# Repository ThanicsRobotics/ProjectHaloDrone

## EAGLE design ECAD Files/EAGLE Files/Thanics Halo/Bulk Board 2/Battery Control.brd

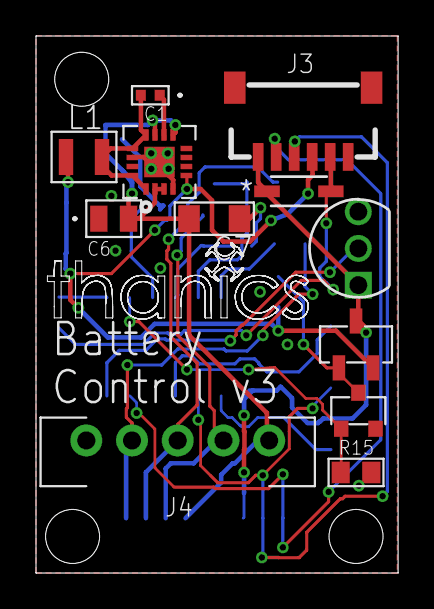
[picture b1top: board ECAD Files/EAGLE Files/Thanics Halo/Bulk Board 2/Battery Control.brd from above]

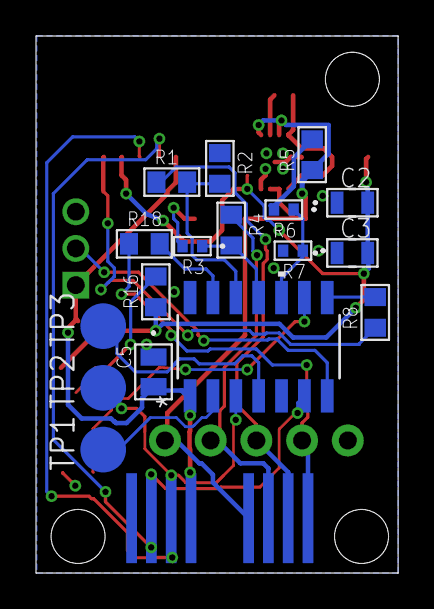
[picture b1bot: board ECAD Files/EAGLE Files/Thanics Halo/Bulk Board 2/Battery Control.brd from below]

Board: 2 copper layers, 20.1 x 29.8 mm, 30 parts (18 on the bottom side), 23 nets.

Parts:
C1: 22nF; G-155-M
C2, C3: 22uF; G-21
C5, C6: 0.1uF; 0805
C7: 10uF; 1206_MLCC
D1: SOD123-M
J1: JST-XH_5POS
J2: SPRING_BTB_8POS_FEMALE
J3: JST_SH_6POS_SIDE
L1: 4.7uH; 1008
R1, R2, R4, R5, R15, R16, R18: 10k; RC0805N
R3, R6, R7: 5k; 0402
R8: 10k 5%; RC0805N
TP1, TP2, TP3: TPB2,54; B2,54
U1: MCP9700-E/TO; TO-92_MC
U2: 2N7002P_MOSFET; SOT-23_(TO-236AB)
U3: DMP3030SN_MOSFET; SC59_MOSFET
U4: TS30012; 16-VQFN
U5: ATTINY20-SSU14S1-M; 14S1-M

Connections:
!RESET: TP3.TP, U5.4
+5V: C5.2, D1.C, J2.5, J3.1, U1.1, U3.D, U5.1
C1: R18.2, U5.13
C2: R1.2, R2.2, U5.12
C3: R3.1, R4.2, U5.11
C4: R6.1, R7.1, U5.10
GND: C2.1, C3.1, C5.1, C6.1, C7.P$1, J1.1, J2.8, J3.6, R2.1, R3.2, R7.2, R15.2, U1.3, U2.S, U4.4, U4.14, U4.15, U4.17, U5.14
unnamed: R16.2, U2.D, U3.G
unnamed: C1.1, U4.10
unnamed: C1.2, L1.P$2, U4.1, U4.12, U4.13, U4.16
unnamed: J1.2, J2.1, R18.1
unnamed: J1.3, J2.2, R1.1
unnamed: J1.4, J2.3, R4.1
unnamed: R5.2, R6.2
unnamed: C6.2, C7.P$2, J1.5, J2.4, R5.1, U4.2, U4.3, U4.9, U4.11
PWR_CONTROL: R15.1, U2.G, U5.9
SCL: J2.7, J3.2, U5.6
SDA: J2.6, J3.3, TP2.TP, U5.3
SENSE: R8.2, U5.8
SWIN: C2.2, C3.2, J3.4, L1.P$1, R16.1, U3.S, U4.5
SWOUT: D1.A, J3.5, R8.1
TEMP: U1.2, U5.7
TPICLK: TP1.TP, U5.2

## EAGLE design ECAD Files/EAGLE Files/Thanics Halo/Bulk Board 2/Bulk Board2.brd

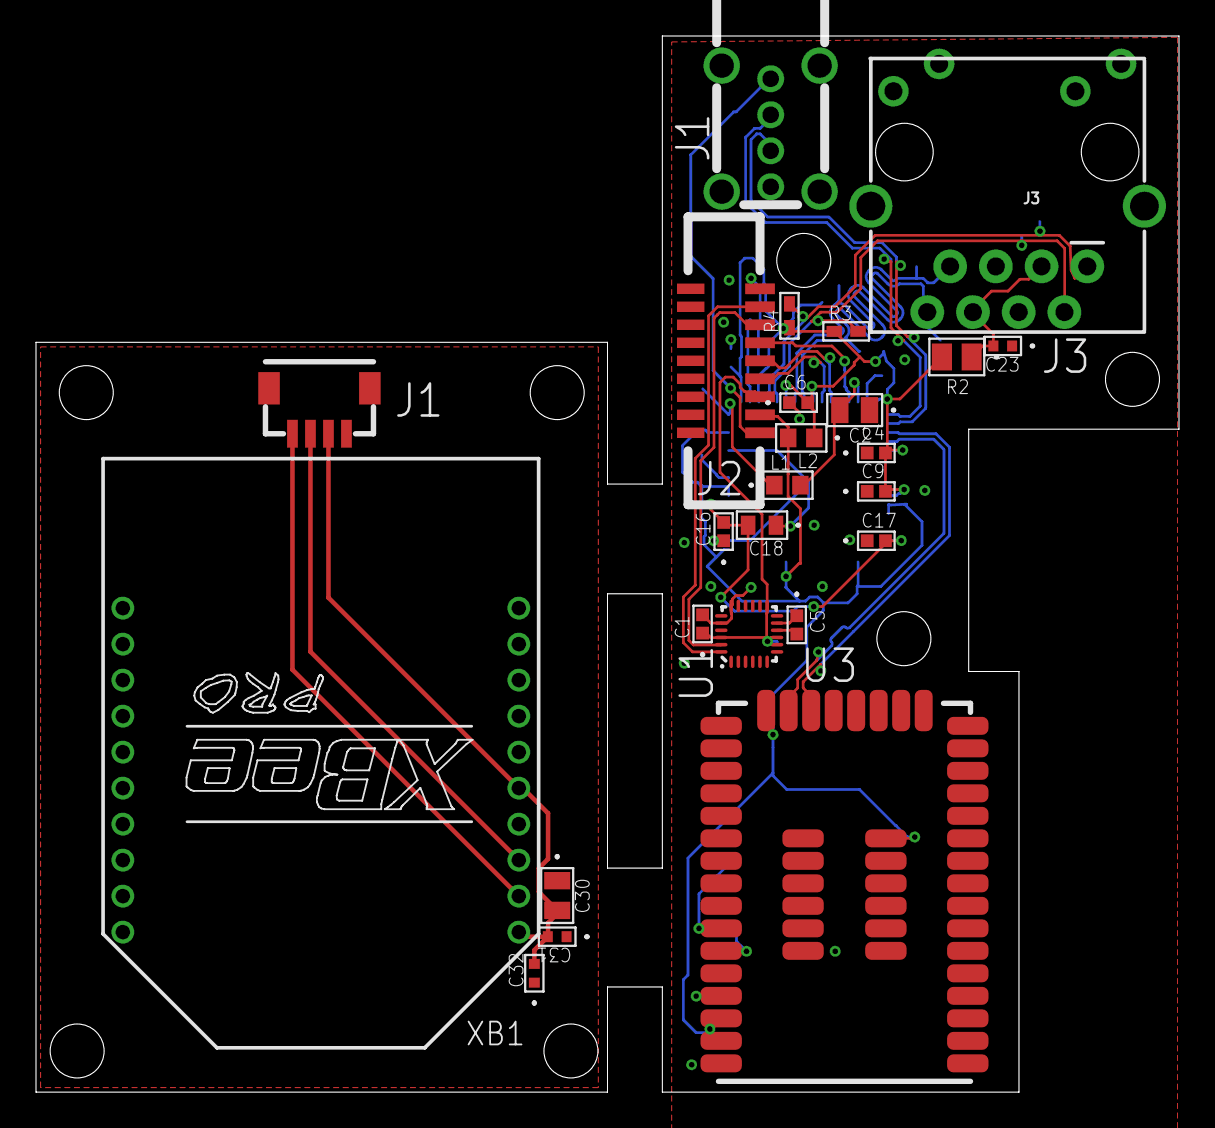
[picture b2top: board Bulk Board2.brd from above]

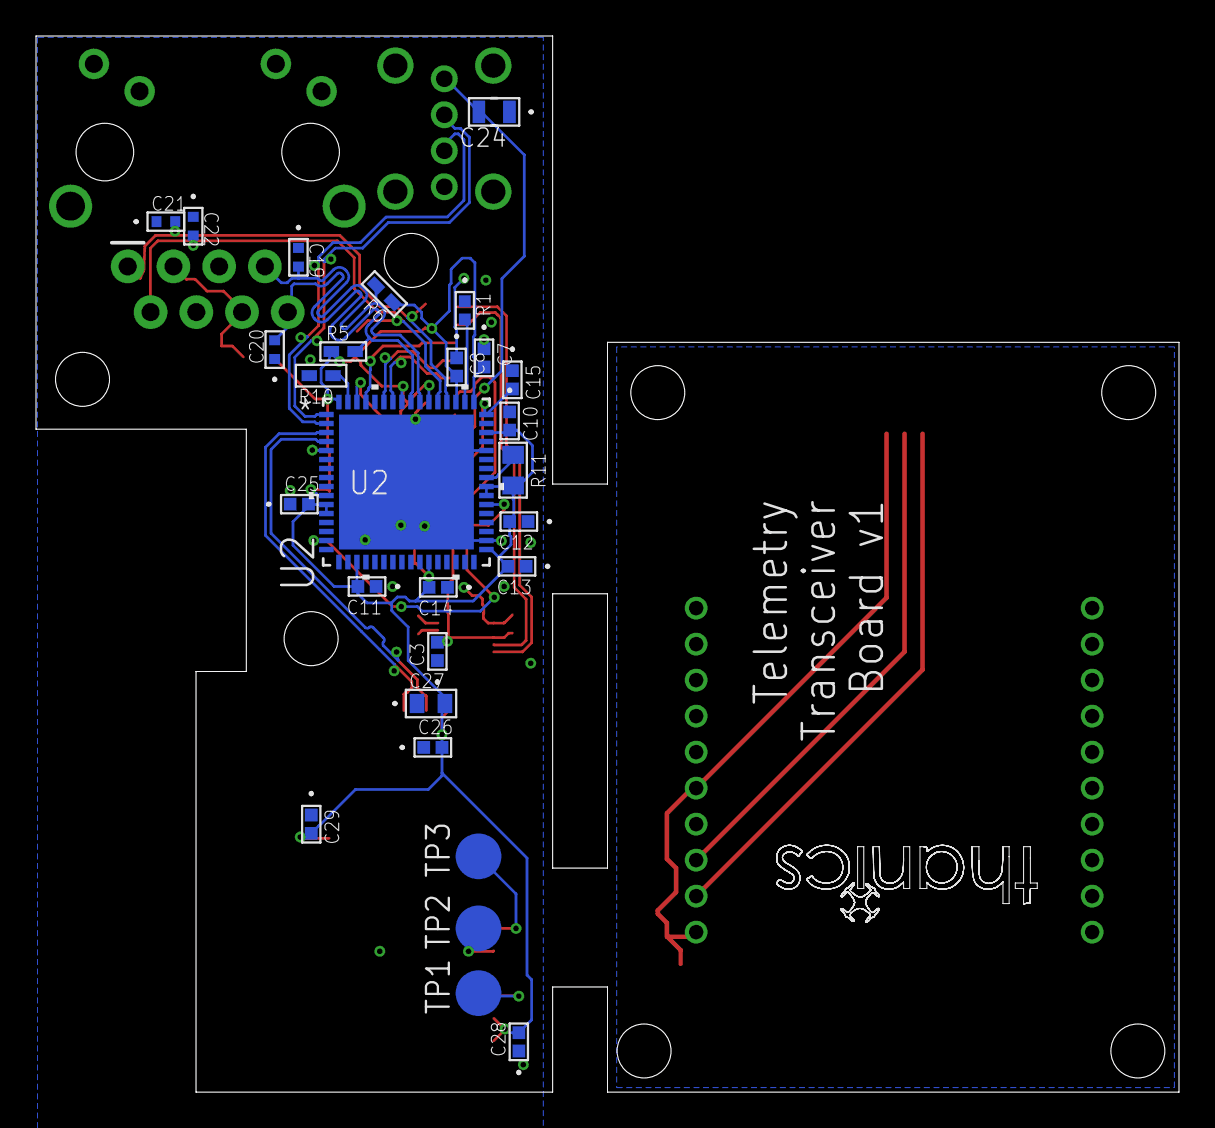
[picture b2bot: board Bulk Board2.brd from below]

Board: 2 copper layers, 63.5 x 58.7 mm, 53 parts (28 on the bottom side), 33 nets.

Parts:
C1, C3, C4, C5, C6, C7, C8, C9, C10, C11, C12, C13, C14, C15, C16, C17, C25, C26, C28, C29: 0.1uF; 0402-M
C2, C30: 1uF; YAG_CC0805
C18, C27: 4.7uF; 0603-M
C19, C20, C21, C22, C31, C32: 16pF; G-155-M
C23: 22nF; G-155-M
C24: 22uF; G-21
J1: USB_A_VERTICAL
J2: 9POS_FFC_CONNECTOR
J3: MAGJACK
J4: JST_SH_4POS
L1, L2: FB; IND_BLM18_0603-M
R1: 12.4k; YAG_R0402-M
R2: 10R; STA_RNCP0805-M
R3, R4, R5, R6: 49R9; RC0402N-M
R10: 12k; RC0402N-M
R11: 10k; RC0805N
TP1, TP2, TP3: TPB2,54; B2,54
U1: QFN40P300X300X105-25N
U2: QFN64_9X9MC-M
U3: WGM110A
XB1: XBEE-PRO

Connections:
1.8V: C1.1, C3.2, J2.3, U1.8, U1.9, U1.13, U1.22
3.3V_A: C4.2, C6.2, C7.2, C8.2, C9.2, L2.1, R2.2, R3.1, R4.1, R5.1, R6.1, U2.5, U2.10, U2.49, U2.51, U2.54, U2.57, U2.64
+3V1: C30.2, C31.2, C32.2, J4.3, XB1.1, XB1.5
+3V3: C10.2, C11.2, C12.2, C13.2, C14.2, C25.2, C26.2, C27.2, C28.2, C29.2, J2.2, L2.2, R11.2, U2.11, U2.12, U2.19, U2.27, U2.33, U2.39, U2.40, U2.46, U3.24, U3.38, U3.39, U3.51
+5V: C24.2, J1.1, J2.1
GND: C1.2, C2.1, C3.1, C4.1, C5.1, C6.1, C7.1, C8.1, C9.1, C10.1, C11.1, C12.1, C13.1, C14.1, C15.1, C16.1, C17.1, C18.1, C19.1, C20.1, C21.1, C22.1, C23.1, C24.1, C25.1, C26.1, C27.1, C28.1, C29.1, J1.4, J1.P$5, J1.P$6, J1.P$7, J1.P$8, J2.9, J3.10, J3.12, J3.M1, J3.M2, R1.1, R10.2, U1.11, U1.18, U1.20, U2.34, U2.44, U2.65, U3.1, U3.16, U3.25, U3.40, U3.42, U3.44, U3.46, U3.48
GND1: C30.1, C31.1, C32.1, J4.4, XB1.10, XB1.14
GPCLK: J2.6, U2.61
unnamed: R11.1, U2.41
unnamed: R10.1, U2.63
unnamed: C15.2, L1.1, U2.48
unnamed: C2.2, L1.2, U2.62
unnamed: TP1.TP, U3.37
unnamed: TP2.TP, U3.35
unnamed: TP3.TP, U3.34
unnamed: C5.2, U1.10
unnamed: R1.2, U2.50
unnamed: C16.2, C17.2, C18.2, U2.15, U2.38
unnamed: C23.2, J3.3, J3.6, R2.1
RX: J4.2, XB1.3
RX_N: C22.2, J3.2, R3.2, U2.53
RX_P: C21.2, J3.1, R4.2, U2.52
SCL: J2.7, U1.23
SDA: J2.8, U1.24
TX: J4.1, XB1.2
TX_N: C20.2, J3.8, R5.2, U2.56
TX_P: C19.2, J3.7, R6.2, U2.55
USB_D2_N: J1.2, U2.1
USB_D2_P: J1.3, U2.2
USB_D3_N: U2.3, U3.22
USB_D3_P: U2.4, U3.23
USB_D_N: J2.4, U2.58
USB_D_P: J2.5, U2.59

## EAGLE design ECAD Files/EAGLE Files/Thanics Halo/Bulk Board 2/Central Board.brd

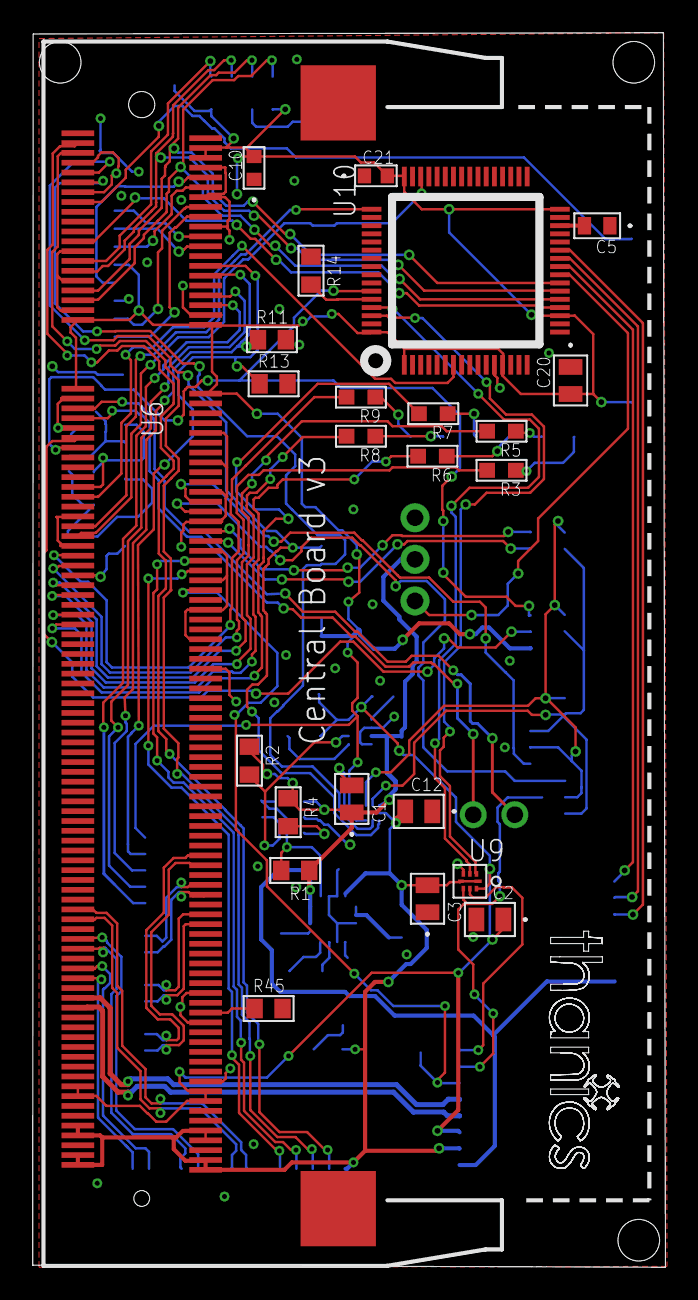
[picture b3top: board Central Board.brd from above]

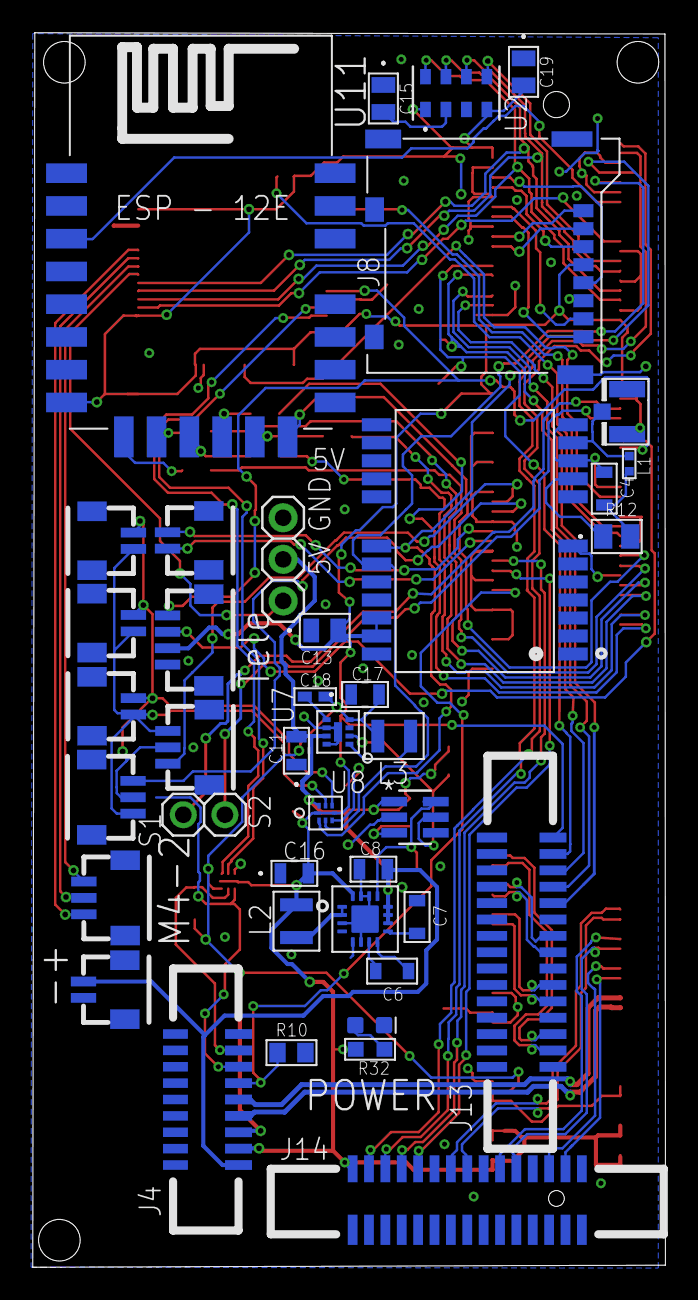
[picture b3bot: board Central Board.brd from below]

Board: 2 copper layers, 38.6 x 75.4 mm, 65 parts (41 on the bottom side), 91 nets.

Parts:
C1, C2, C3, C12, C13, C20: 0.1uF; 0805
C4, C6, C7: 10nF; 0603_CAPACITOR
C5: 4.7uF; 0603-M
C8, C11, C17: 10uF; G-21
C10, C21: 2.2uF; G-188-M
C15, C19: 1uF; YAG_CC0805
C16: 22uF; G-21
C18: 560pF; CC0402N-M
D1: GREEN; LED-0603
J1, J2, J6, J7, J9: JST_SH_2POS
J3: JST_SH_4POS
J4: 9POS_FFC_CONNECTOR
J5: U.FL
J8: MICROSD
J10, J11, J12: JST_SH_3POS
J13, J14: 15POS_FFC_CONNECTOR
JP1: 1X02
JP2: 1X03
L1: 27 nH; 0402_INDUCTOR
L2, L3: 470nH; 1008_INDUCTOR
R1, R2, R4, R10, R11, R13, R14, R45: 10k; RC0805N
R3, R5, R6, R7, R8, R9, R32: 20R; RC0603N-M
R12: 10; STA_RNCP0805-M
U2: LGA8-M
U3: LM3880MF-1AA/NOPBMF06A-M; MF06A-M
U4: NEO-M8
U5: TPS6209; VQFN16
U6: SO-DIMM
U7: MIC23050; MLF(ML)_8PIN
U8, U9: 8-UMLP
U10: LQFP64
U11: ESP12E-SMD

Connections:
1.8V: C2.1, C17.2, C18.2, J4.3, L3.P$2, U6.183, U6.184, U6.185, U6.186, U7.4, U9.8
+3V3: C3.2, C10.2, C12.2, C13.2, C16.2, C19.2, C20.2, C21.2, J3.3, J4.2, J8.4, J13.15, J14.15, L2.P$2, R32.2, U2.1, U2.4, U4.22, U4.23, U5.16, U6.4, U6.6, U6.39, U6.40, U6.41, U6.42, U6.191, U6.192, U6.193, U6.194, U6.197, U6.198, U6.199, U6.200, U8.1, U8.5, U9.1, U9.5, U10.1, U10.13, U10.19, U10.32, U10.48, U10.64, U11.VCC
+5V: C1.1, C8.2, C11.2, J4.1, J6.1, JP2.2, R1.1, R2.1, R4.1, U3.1, U5.10, U5.11, U5.12, U7.7, U8.8
C0_C_N: J13.8, U6.144
C0_C_P: J13.9, U6.142
C0_D0_N: J13.2, U6.138
C0_D0_P: J13.3, U6.136
C0_D1_N: J13.5, U6.150
C0_D1_P: J13.6, U6.148
C0_IO0: J13.11, U6.36
C0_IO1: J13.12, U6.34
C1_C_N: J14.8, U6.149
C1_C_P: J14.9, U6.147
C1_D0_N: J14.2, U6.161
C1_D0_P: J14.3, U6.159
C1_D1_N: J14.5, U6.155
C1_D1_P: J14.6, U6.153
C1_IO0: J14.11, U6.78
C1_IO1: J14.12, U6.76
GND: C1.2, C2.2, C3.1, C4.1, C5.1, C7.1, C8.1, C10.1, C11.1, C12.1, C13.1, C15.1, C16.1, C17.1, C19.1, C20.1, C21.1, D1.C, J3.4, J4.9, J5.P$1, J5.P$2, J6.2, J8.6, J8.9, J8.10, J8.11, J8.12, J8.13, J13.1, J13.4, J13.7, J13.10, J14.1, J14.4, J14.7, J14.10, JP2.3, R10.2, R11.2, R13.2, R14.1, R45.2, U2.3, U3.2, U4.7, U4.10, U4.12, U4.13, U4.24, U5.3, U5.5, U5.6, U5.14, U5.15, U5.17, U6.1, U6.7, U6.8, U6.13, U6.14, U6.19, U6.20, U6.25, U6.26, U6.31, U6.32, U6.37, U6.38, U6.43, U6.44, U6.49, U6.50, U6.55, U6.56, U6.61, U6.62, U6.67, U6.68, U6.73, U6.74, U6.79, U6.80, U6.85, U6.86, U6.91, U6.92, U6.97, U6.98, U6.103, U6.104, U6.109, U6.110, U6.115, U6.116, U6.121, U6.122, U6.127, U6.133, U6.134, U6.139, U6.140, U6.145, U6.146, U6.151, U6.152, U6.157, U6.163, U6.164, U6.169, U6.170, U6.181, U6.182, U6.187, U6.188, U6.195, U6.196, U6.G1, U6.G2, U7.6, U7.8, U7.EP, U8.4, U9.4, U10.12, U10.18, U10.31, U10.47, U10.63, U11.GND
GPCLK1: J4.6, R10.1, U6.82
I2C_MPU_SCL: U9.3, U10.61
I2C_MPU_SDA: U9.2, U10.62
I2C_SCL: U4.19, U6.11, U8.3
I2C_SCL_1V8: J4.7, U9.6
I2C_SCL_5V: J1.2, J2.2, J7.2, J10.2, J11.2, U8.6
I2C_SDA: U4.18, U6.9, U8.2
I2C_SDA_1V8: J4.8, U9.7
I2C_SDA_5V: J1.1, J2.1, J7.1, J10.1, J11.1, U8.7
ID_SD: U6.15, U11.CH_PD
INT_A: J10.3, U6.64
INT_B: J11.3, U6.66
MOTOR1: JP2.1, U10.24
MOTOR2: J12.1, U10.25
MOTOR3: J12.2, U10.26
MOTOR4: J12.3, U10.27
unnamed: J5.P$3, L1.P$1, U4.11
unnamed: C6.2, U5.7
unnamed: C6.1, U5.8
unnamed: D1.A, R32.1
unnamed: R1.2, U3.6, U5.13
unnamed: R2.2, U3.5, U7.2
unnamed: R3.1, U11.CS0
unnamed: R5.1, U11.MISO
unnamed: R6.1, U11.GPIO9
unnamed: R7.1, U11.GPIO10
unnamed: C5.2, U10.30
unnamed: C15.2, U2.2
unnamed: R12.1, U4.9
unnamed: R8.1, U11.MOSI
unnamed: R9.1, U11.SCLK
unnamed: R14.2, U10.60
unnamed: C4.2, L1.P$2, R12.2
unnamed: C7.2, U5.9
unnamed: L2.P$1, U5.1, U5.2
unnamed: L3.P$1, U7.1
unnamed: C18.1, U7.5
unnamed: R45.1, U6.168
NRST: U6.63, U10.7
POWER_SEQ_EN: R4.2, U3.3
SCL0: J13.13, R11.1, U6.30
SCL1: J14.13, U6.5
SDA0: J13.14, R13.1, U6.28
SDA1: J14.14, U6.3
SDX_CLK: J8.5, U6.10
SDX_CMD: J8.3, U6.12
SDX_D0: J8.7, U6.16
SDX_D1: J8.8, U6.18
SDX_D2: J8.1, U6.22
SDX_D3: J8.2, U6.24
SD_CLK: R9.2, U6.75
SD_CMD: R3.2, U6.77
SD_D0: R5.2, U6.81
SD_D1: R8.2, U6.83
SD_D2: R6.2, U6.87
SD_D3: R7.2, U6.89
SERVO1: JP1.1, U6.45
SERVO2: JP1.2, U6.47
SPI_CS0: U2.5, U6.27
SPI_CS1: U6.23, U10.20
SPI_MISO: U2.6, U6.29, U10.22
SPI_MOSI: U2.7, U6.33, U10.23
SPI_SCLK: U2.8, U6.35, U10.21
SWCLK: U6.69, U10.49
SWDIO: U6.71, U10.46
UART2_RX: J9.2, U6.72
UART2_TX: J9.1, U6.70
USART1_RX: J3.1, U6.53, U10.59
USART1_TX: J3.2, U6.51
USB_D_N: J4.4, U6.167
USB_D_P: J4.5, U6.165

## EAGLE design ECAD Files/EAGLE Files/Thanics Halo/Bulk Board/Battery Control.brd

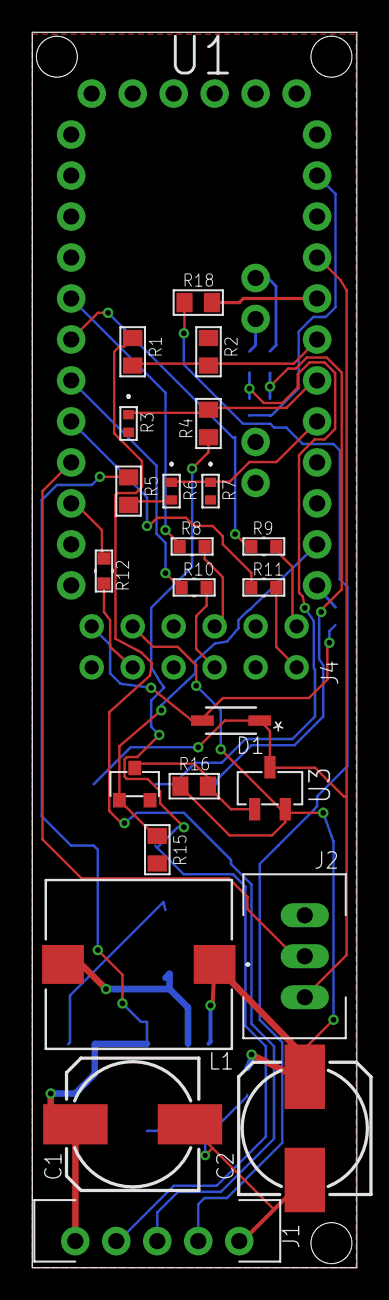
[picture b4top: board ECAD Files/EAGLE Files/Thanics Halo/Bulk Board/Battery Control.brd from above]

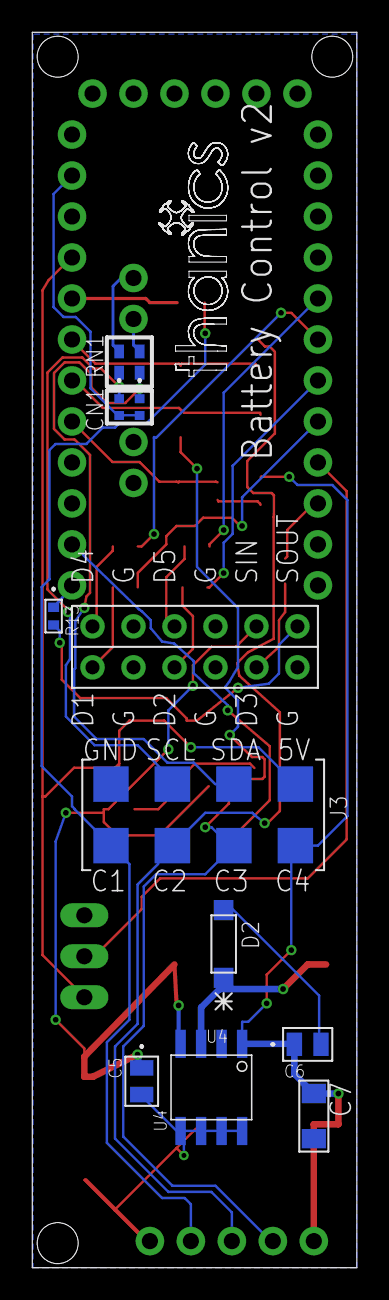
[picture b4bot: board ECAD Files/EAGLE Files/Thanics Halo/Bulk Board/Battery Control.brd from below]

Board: 2 copper layers, 20.1 x 76.6 mm, 36 parts (12 on the bottom side), 32 nets.

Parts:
C1: 100uF; 0810_POLCAP
C2: 330uF; 0807_POLCAP
C3, C4: 1000pF; G-155-M
C5, C6: 0.1uF; 0805
C7: 10uF; 1206_MLCC
D1: SOD123-M
D2: NRVTS245ESF_DIODE; SOD123
J1: JST-XH_5POS
J2: DS18B20_TEMP; JST-XH_3POS
J3: 7_PIN_POGO_CONNECTOR_FEMALE; 7_PIN_CONNECTOR_FEMALE
J4: 12_PIN_RIBBON_CONNECTOR
L1: 200uH; IND_BOURNS_SDR1105
R1, R2, R4, R5, R15, R16, R18: 10k; RC0805N
R3, R6, R7, R13: 5k; 0402
R8, R9, R10, R11: 90.9; RC0603N
R12: 140; RC0603N
R14, R17: 75; RC0402N-M
U1: PRO-MINI-2
U2: 2N7002P_MOSFET; SOT-23_(TO-236AB)
U3: DMP3030SN_MOSFET; SC59_MOSFET
U4: SI-8050W_SWITCH_SUPPLY; SOP8

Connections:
GND: C1.-, C2.-, C3.2, C4.2, C5.2, C6.2, C7.P$2, D2.A, J1.1, J2.P$3, J3.5, J4.P$2, J4.P$4, J4.P$6, J4.P$8, J4.P$10, R2.1, R3.2, R7.2, R15.2, U1.GND, U1.GND1, U2.S, U4.5, U4.6, U4.7, U4.8
unnamed: R8.1, U1.D2
unnamed: J4.P$9, R8.2
unnamed: J2.P$2, U1.D6
unnamed: D1.C, J2.P$1, J3.8, U1.VCC, U3.D
unnamed: R14.2, U1.A4
unnamed: R17.2, U1.A5
unnamed: J1.2, J3.1, R18.1
unnamed: J1.3, J3.2, R1.1
unnamed: R1.2, R2.2, U1.A1
unnamed: R3.1, R4.2, U1.A2
unnamed: J1.4, J3.3, R4.1
unnamed: R5.2, R6.2
unnamed: R6.1, R7.1, U1.A3
unnamed: C1.+, C6.1, C7.P$1, J1.5, J3.4, R5.1, U4.1
unnamed: R9.1, U1.D3
unnamed: J4.P$7, R9.2
unnamed: R10.1, U1.D4
unnamed: J4.P$3, R10.2
unnamed: R11.1, U1.D5
unnamed: J4.P$1, R11.2
unnamed: R12.1, U1.D7
unnamed: J4.P$5, R12.2
unnamed: R13.1, U1.D10
unnamed: R16.2, U2.D, U3.G
unnamed: R15.1, U1.D11, U2.G
unnamed: R18.2, U1.A0
unnamed: D2.C, L1.2, U4.3
unnamed: C3.1, J3.7, R14.1
unnamed: C4.1, J3.6, R17.1
SWIN: C2.+, C5.1, J4.P$11, L1.1, R16.1, U3.S, U4.4
SWOUT: D1.A, J4.P$12, R13.2

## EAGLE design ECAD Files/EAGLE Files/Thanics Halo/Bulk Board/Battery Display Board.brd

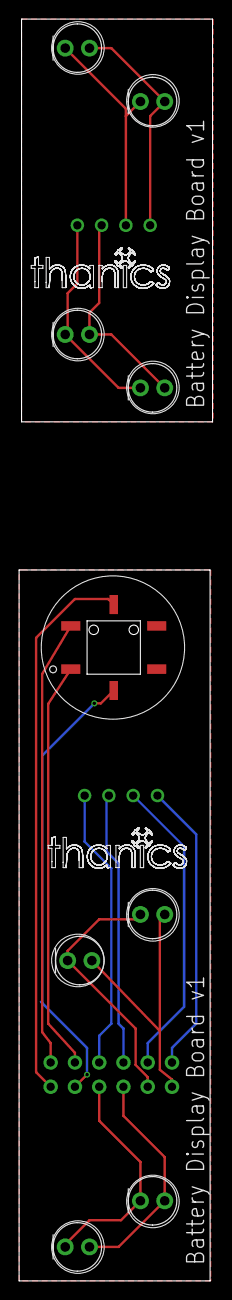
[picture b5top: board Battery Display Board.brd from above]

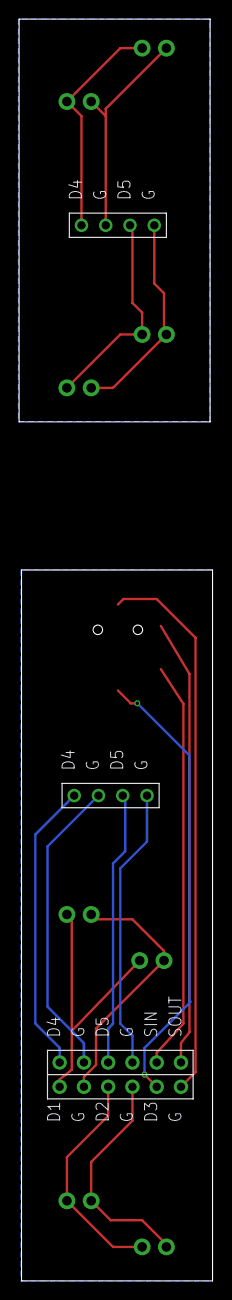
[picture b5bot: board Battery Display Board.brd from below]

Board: 2 copper layers, 20.2 x 132.1 mm, 12 parts (3 on the bottom side), 11 nets.

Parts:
U$1, U$3, U$4, U$5, U$6, U$7, U$8, U$9: VAOL-5LSBY2_BLUE_LED; 5MM_LED
U$2: LED_TACT_SWITCH
U$10: 12_PIN_RIBBON_CONNECTOR
U$11, U$12: 4_PIN_RIBBON_CONNECTOR

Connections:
GND: U$1.C, U$2.5, U$3.C, U$4.C, U$5.C, U$10.P$2, U$10.P$4, U$10.P$6, U$10.P$8, U$10.P$10, U$11.P$2, U$11.P$4
GND2: U$6.C, U$7.C, U$8.C, U$9.C, U$12.P$2, U$12.P$4
unnamed: U$1.A, U$3.A, U$10.P$1
unnamed: U$4.A, U$5.A, U$10.P$3
unnamed: U$2.6, U$10.P$5
unnamed: U$10.P$7, U$11.P$1
unnamed: U$10.P$9, U$11.P$3
unnamed: U$2.1, U$10.P$11
unnamed: U$2.3, U$10.P$12
unnamed: U$6.A, U$7.A, U$12.P$1
unnamed: U$8.A, U$9.A, U$12.P$3

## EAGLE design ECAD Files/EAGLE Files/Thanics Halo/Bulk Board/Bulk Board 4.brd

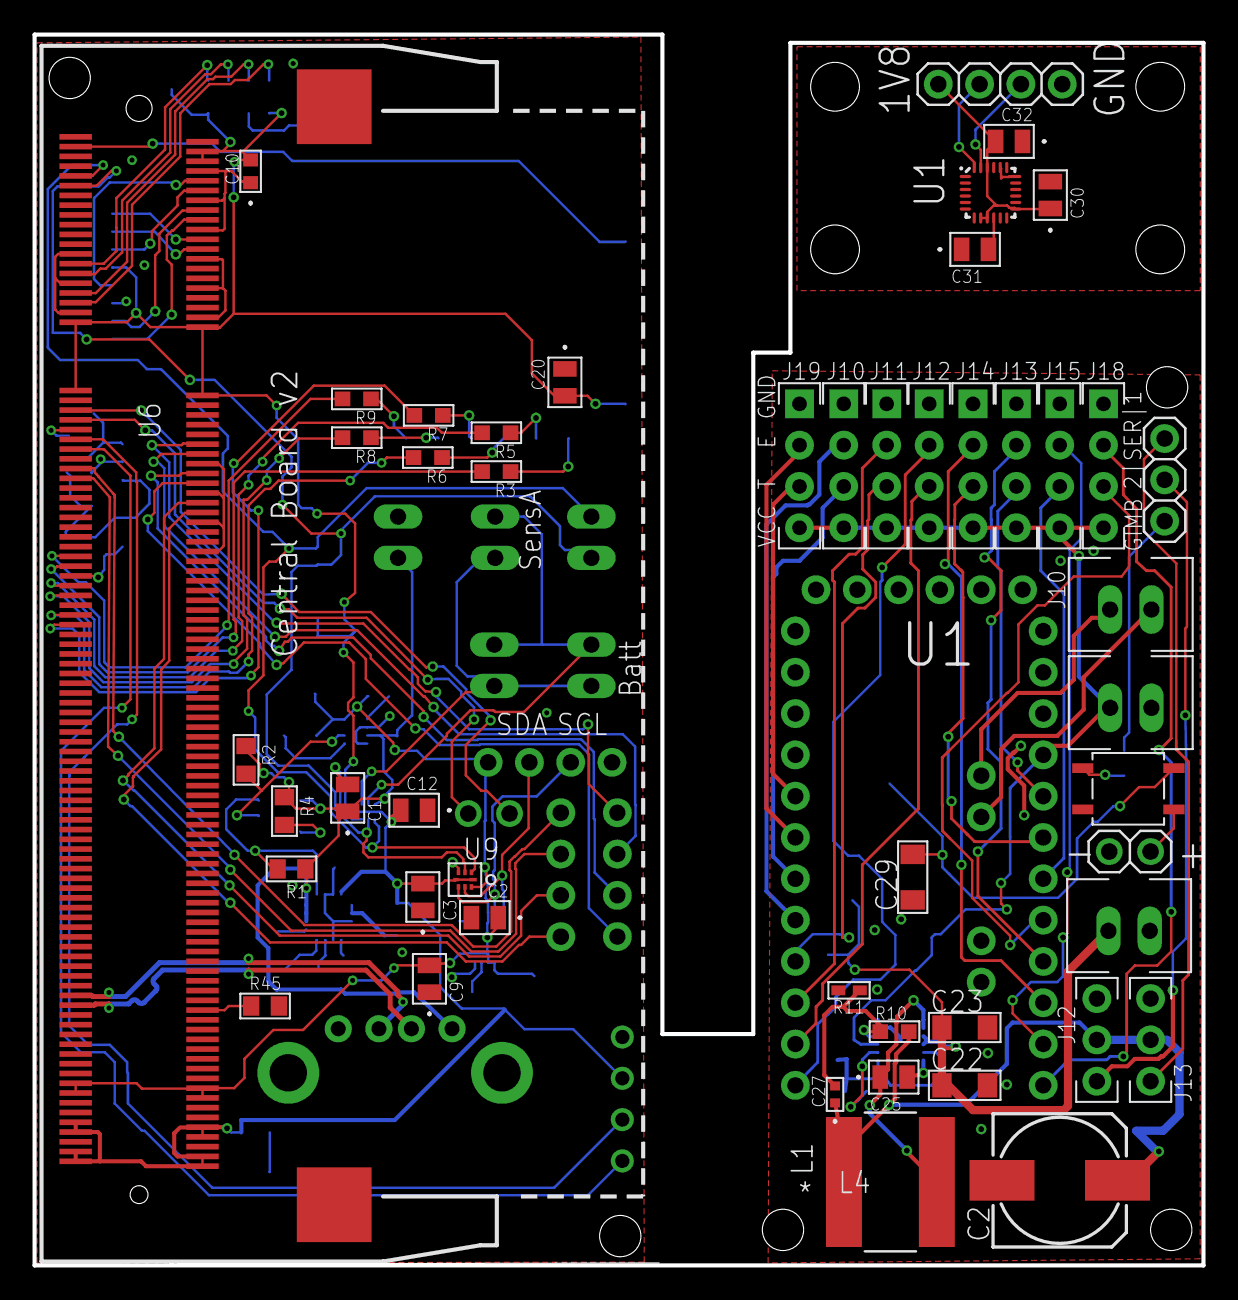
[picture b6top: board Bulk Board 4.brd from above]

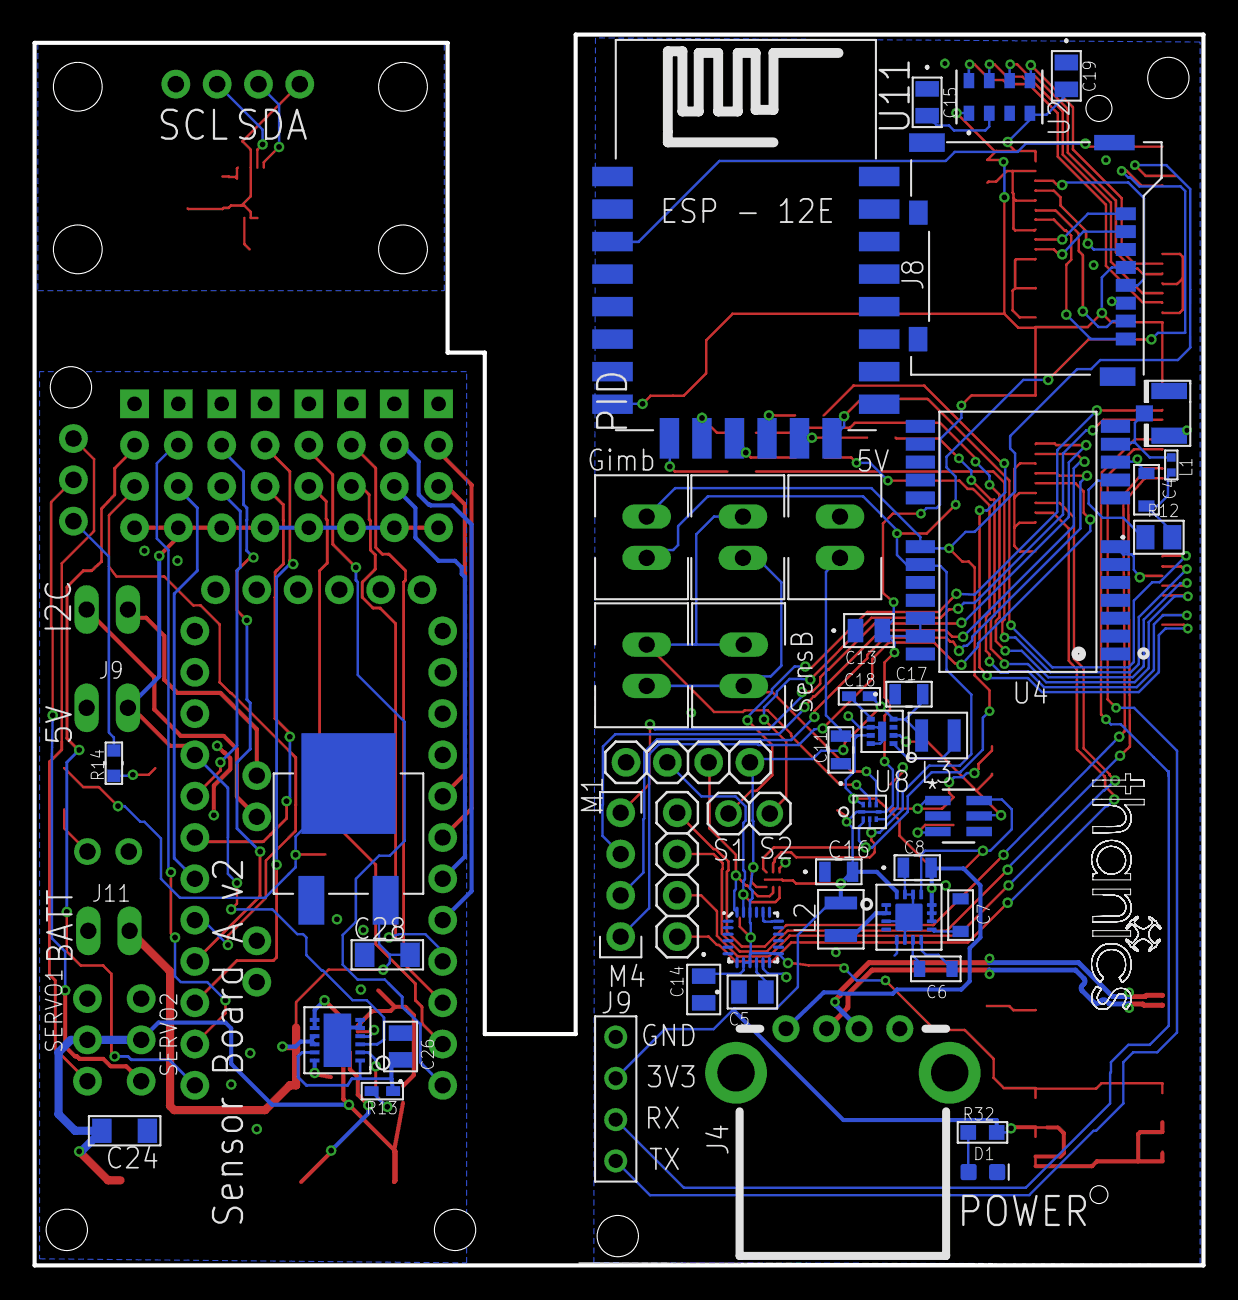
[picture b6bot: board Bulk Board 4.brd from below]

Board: 2 copper layers, 71.9 x 75.7 mm, 97 parts (47 on the bottom side), 101 nets.

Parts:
C1, C2, C3, C5, C9, C12, C13, C14, C20, C25, C26, C30, C31, C32: 0.1uF; 0805
C4, C6, C7: 10nF; 0603_CAPACITOR
C8, C11, C17: 10uF; G-21
C10: 2.2uF; G-188-M
C15, C19: 1uF; YAG_CC0805
C16: 22uF; G-21
C18: 560pF; CC0402N-M
C21: 100uF; 0810_POLCAP
C22, C23, C24, C28, C29: 10uF; 1206_MLCC
C27: 16pF; G-155-M
D1: GREEN; LED-0603
J1, J16: POWER_CONNECTOR; XH_CONNECTOR
J2, J3, J6, J7, J17: I2C_CONNECTOR; XH_CONNECTOR
J4: USB_A_RECEPT
J5: U.FL
J8: MICROSD
J9: 4_PIN_TELE_CONNECTOR
J10, J11, J12, J13, J14, J15, J18, J19: HC-SR04; HC-SR04_FOOTPRINT
J20, J21: SERVO_CONNECTOR
J22: GIMBAL_POWER_CONNECTOR; XH_CONNECTOR
JP1, JP4: 1X02
JP2, JP3, JP6: 1X04
JP5: 1X03
L1: 27 nH; 0402_INDUCTOR
L2, L3: 470nH; 470NH_INDUCTOR
L4: 3.3uH; IND_BOURNS_SRN8040
R1, R2, R4, R45: 10k; RC0805N
R3, R5, R6, R7, R8, R9, R32: 20R; RC0603N-M
R10: 499k; RC0603N-M
R11, R13: 95.3k; RC0402N-M
R12: 10; STA_RNCP0805-M
R14: 340R; RC0603N
U1, U15: QFN40P300X300X105-25N
U2: LGA8-M
U3: LM3880MF-1AA/NOPBMF06A-M; MF06A-M
U4: NEO-M8
U5: TPS6209; VQFN16
U6: SO-DIMM
U7: MIC23050; MLF(ML)_8PIN
U8, U9: 8-UMLP
U10: PRO-MINI-2
U11: ESP12E-SMD
U12: 12LD4X3DFN
U13: 4-SOP
U14: DPAK
U$12: 4_PIN_CONNECTOR

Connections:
1.8V: C2.1, C9.2, C14.1, C17.2, C18.2, JP3.1, L3.P$2, U1.8, U1.9, U1.13, U1.22, U6.183, U6.184, U6.185, U6.186, U7.4, U9.8
1.8V1: C30.1, C32.2, JP6.1, U15.8, U15.9, U15.13, U15.22
+3V3: C3.2, C10.2, C12.2, C13.2, C16.2, C19.2, C20.2, J8.4, J9.3, L2.P$2, R32.2, U2.1, U2.4, U4.22, U4.23, U5.16, U6.4, U6.6, U6.39, U6.40, U6.41, U6.42, U6.191, U6.192, U6.193, U6.194, U6.197, U6.198, U6.199, U6.200, U8.1, U8.5, U9.1, U9.5, U11.VCC
+5V: C1.1, C8.2, C11.2, J1.1, J4.1, R1.1, R2.1, R4.1, U3.1, U5.10, U5.11, U5.12, U7.7, U8.8
+5V1: J10.VCC, J11.VCC, J12.VCC, J13.VCC, J14.VCC, J15.VCC, J16.1, J18.VCC, J19.VCC, U10.VCC, U12.3
+12V: C29.P$2, U13.4, U14.2
ECHO1: J19.ECHO, U10.D3
ECHO2: J10.ECHO, U10.D5
ECHO3: J11.ECHO, U10.D7
ECHO4: J12.ECHO, U10.D9
ECHO5: J13.ECHO, U10.D13
ECHO6: J14.ECHO, U10.D12
ECHO7: J15.ECHO, U10.D11
ECHO8: J18.ECHO, U10.D10
GIMBAL: JP5.3, R14.2
GND: C1.2, C2.2, C3.1, C4.1, C5.1, C7.1, C8.1, C9.1, C10.1, C11.1, C12.1, C13.1, C14.2, C15.1, C16.1, C17.1, C19.1, C20.1, D1.C, J1.2, J4.4, J4.5, J4.6, J5.P$1, J5.P$2, J8.6, J8.9, J8.10, J8.11, J8.12, J8.13, J9.4, JP3.4, R45.2, U1.11, U1.18, U1.20, U2.3, U3.2, U4.7, U4.10, U4.12, U4.13, U4.24, U5.3, U5.5, U5.6, U5.14, U5.15, U5.17, U6.1, U6.7, U6.8, U6.13, U6.14, U6.19, U6.20, U6.25, U6.26, U6.31, U6.32, U6.37, U6.38, U6.43, U6.44, U6.49, U6.50, U6.55, U6.56, U6.61, U6.62, U6.67, U6.68, U6.73, U6.74, U6.79, U6.80, U6.85, U6.86, U6.91, U6.92, U6.97, U6.98, U6.103, U6.104, U6.109, U6.110, U6.115, U6.116, U6.121, U6.122, U6.127, U6.133, U6.134, U6.139, U6.140, U6.145, U6.146, U6.151, U6.152, U6.157, U6.163, U6.164, U6.169, U6.170, U6.181, U6.182, U6.187, U6.188, U6.195, U6.196, U6.G1, U6.G2, U7.6, U7.8, U7.EP, U8.4, U9.4, U11.GND
GND1: C21.-, C22.P$2, C23.P$2, C24.P$1, C26.2, C28.P$1, C29.P$1, J10.GND, J11.GND, J12.GND, J13.GND, J14.GND, J15.GND, J16.2, J18.GND, J19.GND, J20.3, J21.3, J22.2, JP4.2, R11.2, U10.GND, U10.GND1, U12.5, U12.6, U12.EP, U13.2, U14.1
GND2: C30.2, C31.1, C32.1, JP6.4, U15.11, U15.18, U15.20
I2C_SCL: J7.1, U4.19, U6.11, U8.3, U9.3
I2C_SCL_1V1: JP6.3, U15.23
I2C_SCL_1V8: JP3.3, U1.23, U9.6
I2C_SCL_5V: J2.1, J3.1, J6.1, U8.6
I2C_SDA: J7.2, U4.18, U6.9, U8.2, U9.2
I2C_SDA_1V1: JP6.2, U15.24
I2C_SDA_1V8: JP3.2, U1.24, U9.7
I2C_SDA_5V: J2.2, J3.2, J6.2, U8.7
ID_SD: U6.3, U11.CH_PD
LED1: JP2.1, U6.57
LED2: JP2.2, U6.59
LED3: JP2.3, U6.64
LED4: JP2.4, U6.66
MOTOR1: U6.52, U$12.1
MOTOR2: U6.54, U$12.2
MOTOR3: U6.58, U$12.3
MOTOR4: U6.60, U$12.4
unnamed: J5.P$3, L1.P$1, U4.11
unnamed: C6.2, U5.7
unnamed: C6.1, U5.8
unnamed: D1.A, R32.1
unnamed: R1.2, U3.6, U5.13
unnamed: R2.2, U3.5, U7.2
unnamed: R3.1, U11.CS0
unnamed: R5.1, U11.MISO
unnamed: R6.1, U11.GPIO9
unnamed: R7.1, U11.GPIO10
unnamed: C5.2, U1.10
unnamed: C15.2, U2.2
unnamed: R12.1, U4.9
unnamed: R8.1, U11.MOSI
unnamed: R9.1, U11.SCLK
unnamed: C27.2, R10.1, R11.1, U12.4
unnamed: C25.2, U12.12
unnamed: C25.1, L4.2, U12.7, U12.8
unnamed: R13.2, U12.2
unnamed: R14.1, U13.1
unnamed: JP4.1, U13.3
unnamed: C31.2, U15.10
unnamed: C4.2, L1.P$2, R12.2
unnamed: C7.2, U5.9
unnamed: L2.P$1, U5.1, U5.2
unnamed: L3.P$1, U7.1
unnamed: C18.1, U7.5
unnamed: R45.1, U6.168
POWER_SEQ_EN: R4.2, U3.3
SCL: J17.1, U10.A5
SDA: J17.2, U10.A4
SDX_CLK: J8.5, U6.10
SDX_CMD: J8.3, U6.12
SDX_D0: J8.7, U6.16
SDX_D1: J8.8, U6.18
SDX_D2: J8.1, U6.22
SDX_D3: J8.2, U6.24
SD_CLK: R9.2, U6.75
SD_CMD: R3.2, U6.77
SD_D0: R5.2, U6.81
SD_D1: R8.2, U6.83
SD_D2: R6.2, U6.87
SD_D3: R7.2, U6.89
SERVO1: JP1.1, U6.45
SERVO2: JP1.2, U6.47
SERVO3: J21.1, JP5.2
SERVO4: J20.1, JP5.1
SPI_CS0: U2.5, U6.27
SPI_MISO: U2.6, U6.29
SPI_MOSI: U2.7, U6.33
SPI_SCLK: U2.8, U6.35
TRIG1: J19.TRIG, U10.D2
TRIG2: J10.TRIG, U10.D4
TRIG3: J11.TRIG, U10.D6
TRIG4: J12.TRIG, U10.D8
TRIG5: J13.TRIG, U10.A0
TRIG6: J14.TRIG, U10.A1
TRIG7: J15.TRIG, U10.A2
TRIG8: J18.TRIG, U10.A3
UART_RX: J9.1, U6.53
UART_TX: J9.2, U6.51
USB_D_N: J4.2, U6.167
USB_D_P: J4.3, U6.165
VDD: C26.1, R13.1, U12.1, U12.11
VOUT: C21.+, C24.P$2, C27.1, J20.2, J21.2, L4.1, R10.2
V_BATT: C22.P$1, C23.P$1, C28.P$2, J22.1, U12.9, U12.10, U14.3

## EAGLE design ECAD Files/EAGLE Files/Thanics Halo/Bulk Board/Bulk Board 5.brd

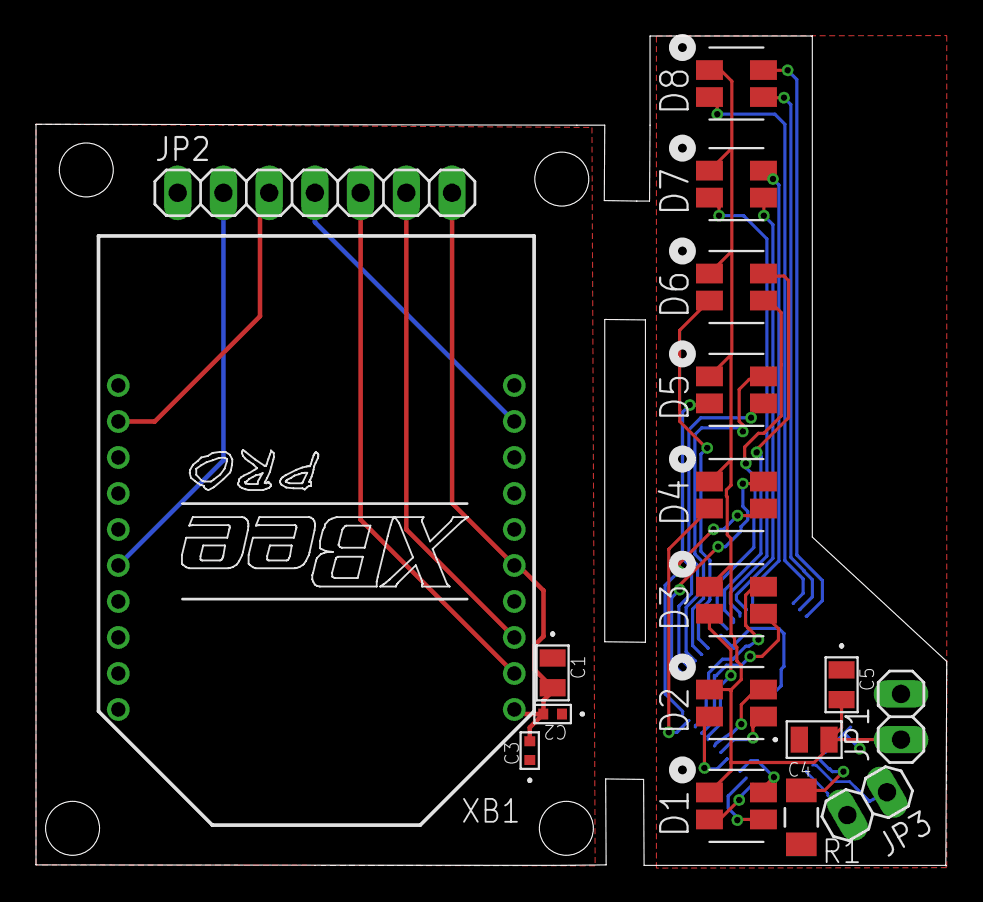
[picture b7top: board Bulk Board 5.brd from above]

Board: 2 copper layers, 50.6 x 46.1 mm, 19 parts (1 on the bottom side), 36 nets.

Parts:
C1, C5: 1uF; YAG_CC0805
C2, C3: 16pF; G-155-M
C4: 0.1uF; 0805
D1, D2, D3, D4, D5, D6, D7, D8: ASMB-MTB0_LED
JP1, JP3: 1X02
JP2: 1X07
R1: 3k3; RC1206N-M
U1: TQFP-48
XB1: XBEE-PRO

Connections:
!CTS: JP2.3, XB1.12
!DTR: JP2.4, XB1.9
!RTS: JP2.2, XB1.16
+3V3: C1.2, C2.2, C3.2, JP2.7, XB1.1, XB1.5
+5V: C4.2, C5.2, D1.1, D2.1, D3.1, D4.1, D5.1, D6.1, D7.1, D8.1, JP1.1, U1.39, U1.40, U1.41
GND: C1.1, C2.1, C3.1, JP2.1, XB1.10, XB1.14
GND1: C4.1, C5.1, JP1.2, R1.1, U1.4, U1.18, U1.19, U1.33, U1.42, U1.43, U1.EP
unnamed: D1.4, U1.1
unnamed: D1.3, U1.2
unnamed: D2.3, U1.6
unnamed: D1.2, U1.3
unnamed: D2.4, U1.5
unnamed: R1.2, U1.44
unnamed: D3.4, U1.8
unnamed: D3.3, U1.9
unnamed: D3.2, U1.10
unnamed: D4.4, U1.11
unnamed: D4.3, U1.12
unnamed: D4.2, U1.13
unnamed: D5.4, U1.14
unnamed: D5.3, U1.15
unnamed: D5.2, U1.16
unnamed: D6.4, U1.17
unnamed: D6.3, U1.20
unnamed: D6.2, U1.21
unnamed: D7.4, U1.22
unnamed: D7.3, U1.23
unnamed: D7.2, U1.24
unnamed: D8.4, U1.25
unnamed: D8.3, U1.26
unnamed: D8.2, U1.27
unnamed: D2.2, U1.7
RX: JP2.6, XB1.3
SCL: JP3.2, U1.46
SDA: JP3.1, U1.45
TX: JP2.5, XB1.2

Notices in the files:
parts and their libraries:
COPYRIGHT: Copyright C 2015 Accelerated Designs. All rights reserved
SparkFun-Connectors: Licensing: Creative Commons ShareAlike 4.0 International - https://creativecommons.org/licenses/by-sa/4.0
